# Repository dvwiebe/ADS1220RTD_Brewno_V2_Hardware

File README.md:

# ADS1220RTD_Brewno_V2_Hardware
RTD Shield Hardware
All the files you need to build your own shield.  The Gerber Files and Excellon drill file included to allow you to go straight
to fabrication.  Alternatively the Eagle files are available.

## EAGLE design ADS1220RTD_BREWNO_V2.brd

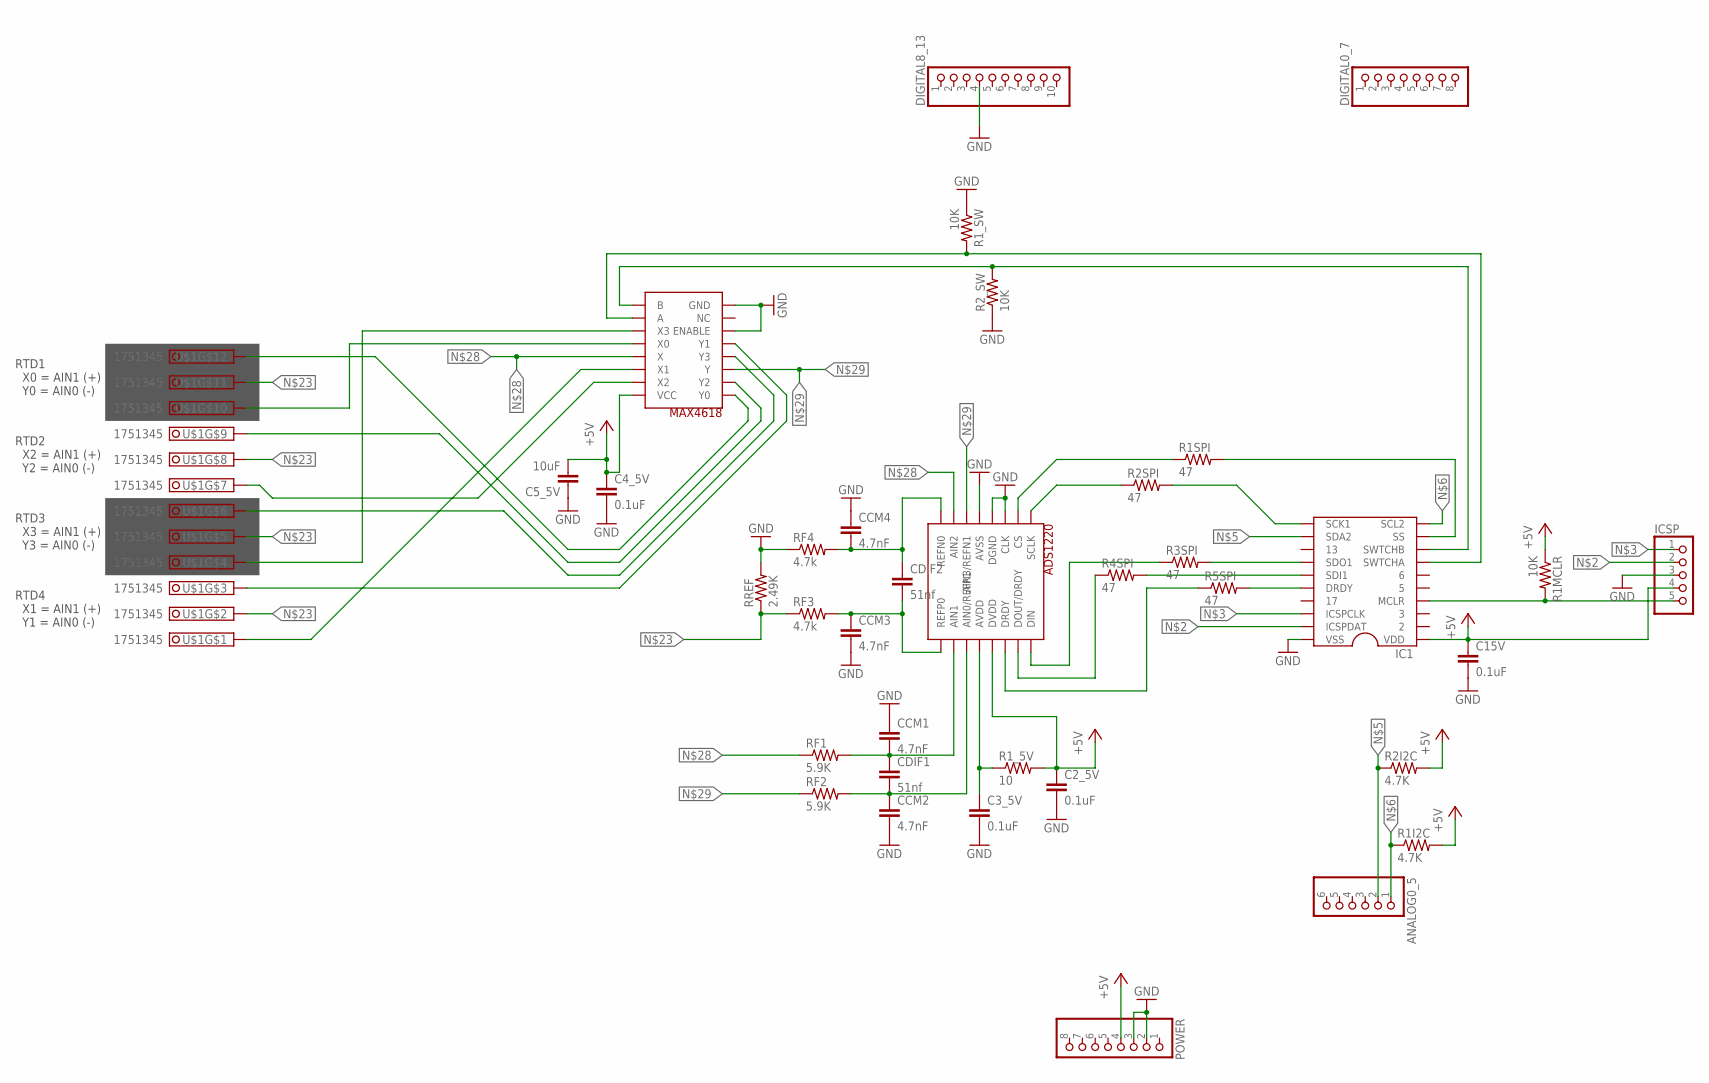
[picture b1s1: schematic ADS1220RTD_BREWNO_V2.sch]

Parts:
ADS1220: ADS1220; TSSOP16
ANALOG0_5: PINHD-1X6; 1X06
C2_5V, C3_5V, C4_5V, C15V: 0.1uF; C0603
C5_5V: 10uF; C0603
CCM1, CCM2, CCM3, CCM4: 4.7nF; C0603
CDIF1, CDIF2: 51nf; C1206
DIGITAL0_7: PINHD-1X8; 1X08
DIGITAL8_13: PINHD-1X10; 1X10
IC1: DIL20
ICSP: PINHD-1X5; 1X05
MAX4618: MAX4618CPE; SO16
POWER: PINHD-1X8; 1X08
R1I2C, R2I2C: 4.7K; R0603
R1MCLR, R1_SW, R2_SW: 10K; R0603
R1SPI, R2SPI, R3SPI, R4SPI, R5SPI: 47; R0603
R1_5V: 10; R0603
RF1, RF2: 5.9K; R0603
RF3, RF4: 4.7k; R0603
RREF: 2.49K; R0603
U$1: 1751345

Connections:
+5V: ADS1220.13 (DVDD), C2_5V.1, C4_5V.1, C5_5V.2, C15V.1, IC1.1 (VDD), ICSP.4, MAX4618.16 (VCC), POWER.4, R1I2C.2, R1MCLR.1, R1_5V.2, R2I2C.2
GND: ADS1220.3 (CLK), ADS1220.4 (DGND), ADS1220.5 (AVSS), C2_5V.2, C3_5V.2, C4_5V.2, C5_5V.1, C15V.2, CCM1.1, CCM2.2, CCM3.2, CCM4.1, DIGITAL8_13.4, IC1.20 (VSS), ICSP.3, MAX4618.6 (ENABLE), MAX4618.8 (GND), POWER.2, POWER.3, R1_SW.1, R2_SW.1, RF4.1, RREF.2
unnamed: IC1.4 (MCLR), ICSP.5, R1MCLR.2
unnamed: IC1.19 (ICSPDAT), ICSP.2
unnamed: IC1.18 (ICSPCLK), ICSP.1
unnamed: IC1.11 (SCK1), R2SPI.2
unnamed: ANALOG0_5.2, IC1.12 (SDA2), R2I2C.1
unnamed: ANALOG0_5.1, IC1.10 (SCL2), R1I2C.1
unnamed: ADS1220.1 (SCLK), R2SPI.1
unnamed: ADS1220.2 (CS), R1SPI.1
unnamed: IC1.9 (SS), R1SPI.2
unnamed: IC1.14 (SDO1), R3SPI.2
unnamed: IC1.15 (SDI1), R4SPI.2
unnamed: ADS1220.14 (DRDY), R5SPI.1
unnamed: ADS1220.12 (AVDD), C3_5V.1, R1_5V.1
unnamed: IC1.16 (DRDY), R5SPI.2
unnamed: ADS1220.16 (DIN), R3SPI.1
unnamed: ADS1220.15 (DOUT/DRDY), R4SPI.1
unnamed: IC1.8 (SWTCHB), MAX4618.9 (B), R2_SW.2
unnamed: IC1.7 (SWTCHA), MAX4618.10 (A), R1_SW.2
unnamed: ADS1220.8 (REFN0), CCM4.2, CDIF2.1, RF4.2
unnamed: ADS1220.9 (REFP0), CCM3.1, CDIF2.2, RF3.2
unnamed: RF3.1, RREF.1, U$1.2, U$1.5, U$1.8, U$1.11
unnamed: ADS1220.11 (AIN0/REFP1), CCM2.1, CDIF1.2, RF2.2
unnamed: ADS1220.10 (AIN1), CCM1.2, CDIF1.1, RF1.2
unnamed: ADS1220.7 (AIN2), MAX4618.13 (X), RF1.1
unnamed: ADS1220.6 (AIN3/REFN1), MAX4618.3 (Y), RF2.1
unnamed: MAX4618.1 (Y0), U$1.12
unnamed: MAX4618.12 (X0), U$1.10
unnamed: MAX4618.2 (Y2), U$1.9
unnamed: MAX4618.4 (Y3), U$1.6
unnamed: MAX4618.15 (X2), U$1.7
unnamed: MAX4618.5 (Y1), U$1.3
unnamed: MAX4618.14 (X1), U$1.1
unnamed: MAX4618.11 (X3), U$1.4

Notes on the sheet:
RTD4 X1 = AIN1 (+) Y1 = AIN0 (-)
RTD3 X3 = AIN1 (+) Y3 = AIN0 (-)
RTD2 X2 = AIN1 (+) Y2 = AIN0 (-)
RTD1 X0 = AIN1 (+) Y0 = AIN0 (-)

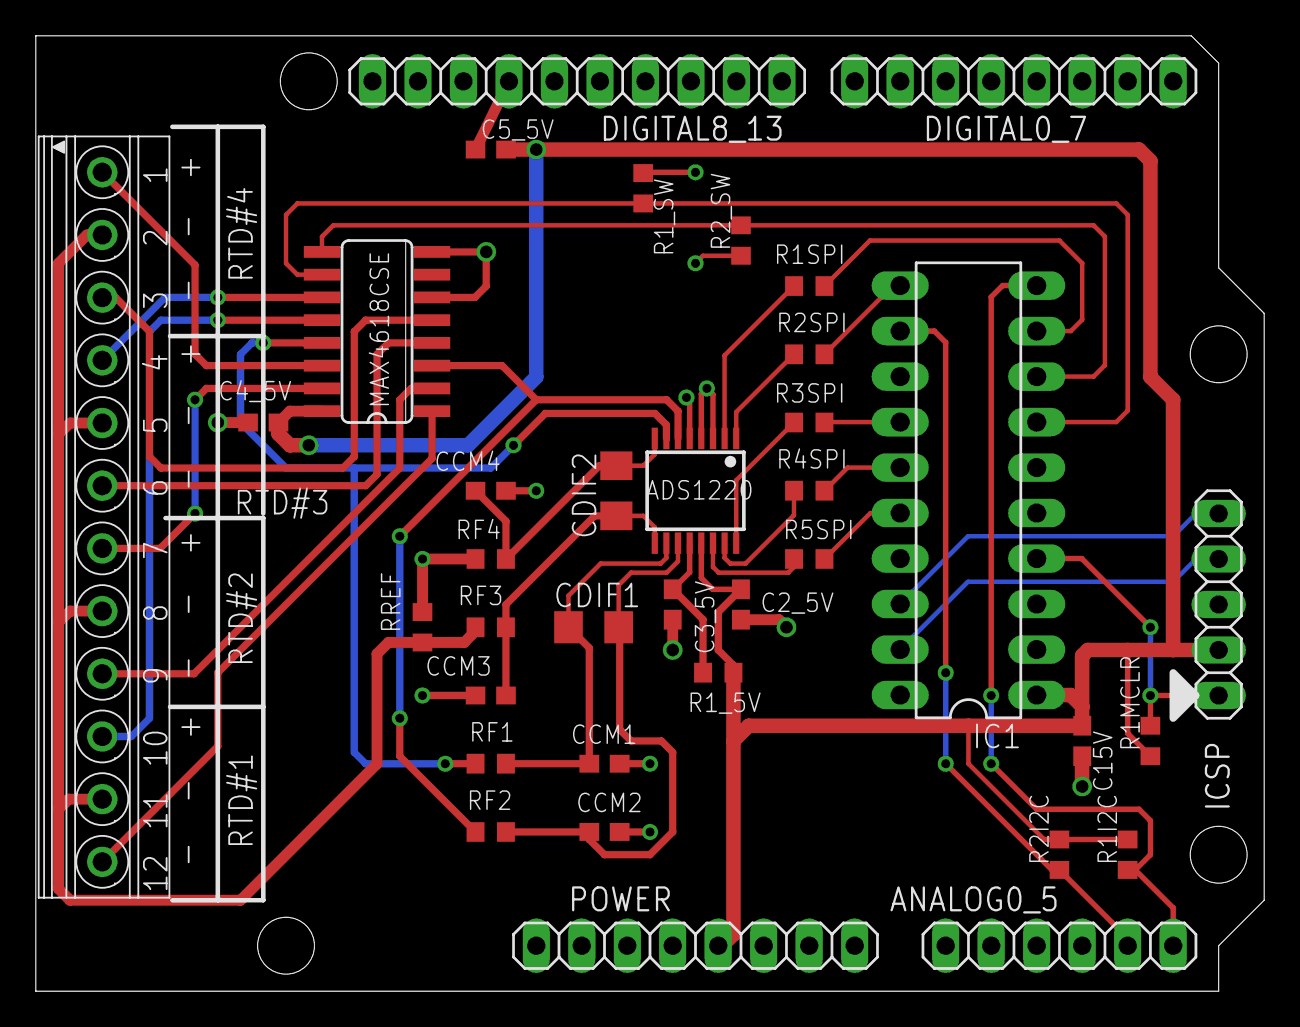
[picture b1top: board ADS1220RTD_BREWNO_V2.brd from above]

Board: 2 copper layers, 68.6 x 53.3 mm, 36 parts (0 on the bottom side), 35 nets.
